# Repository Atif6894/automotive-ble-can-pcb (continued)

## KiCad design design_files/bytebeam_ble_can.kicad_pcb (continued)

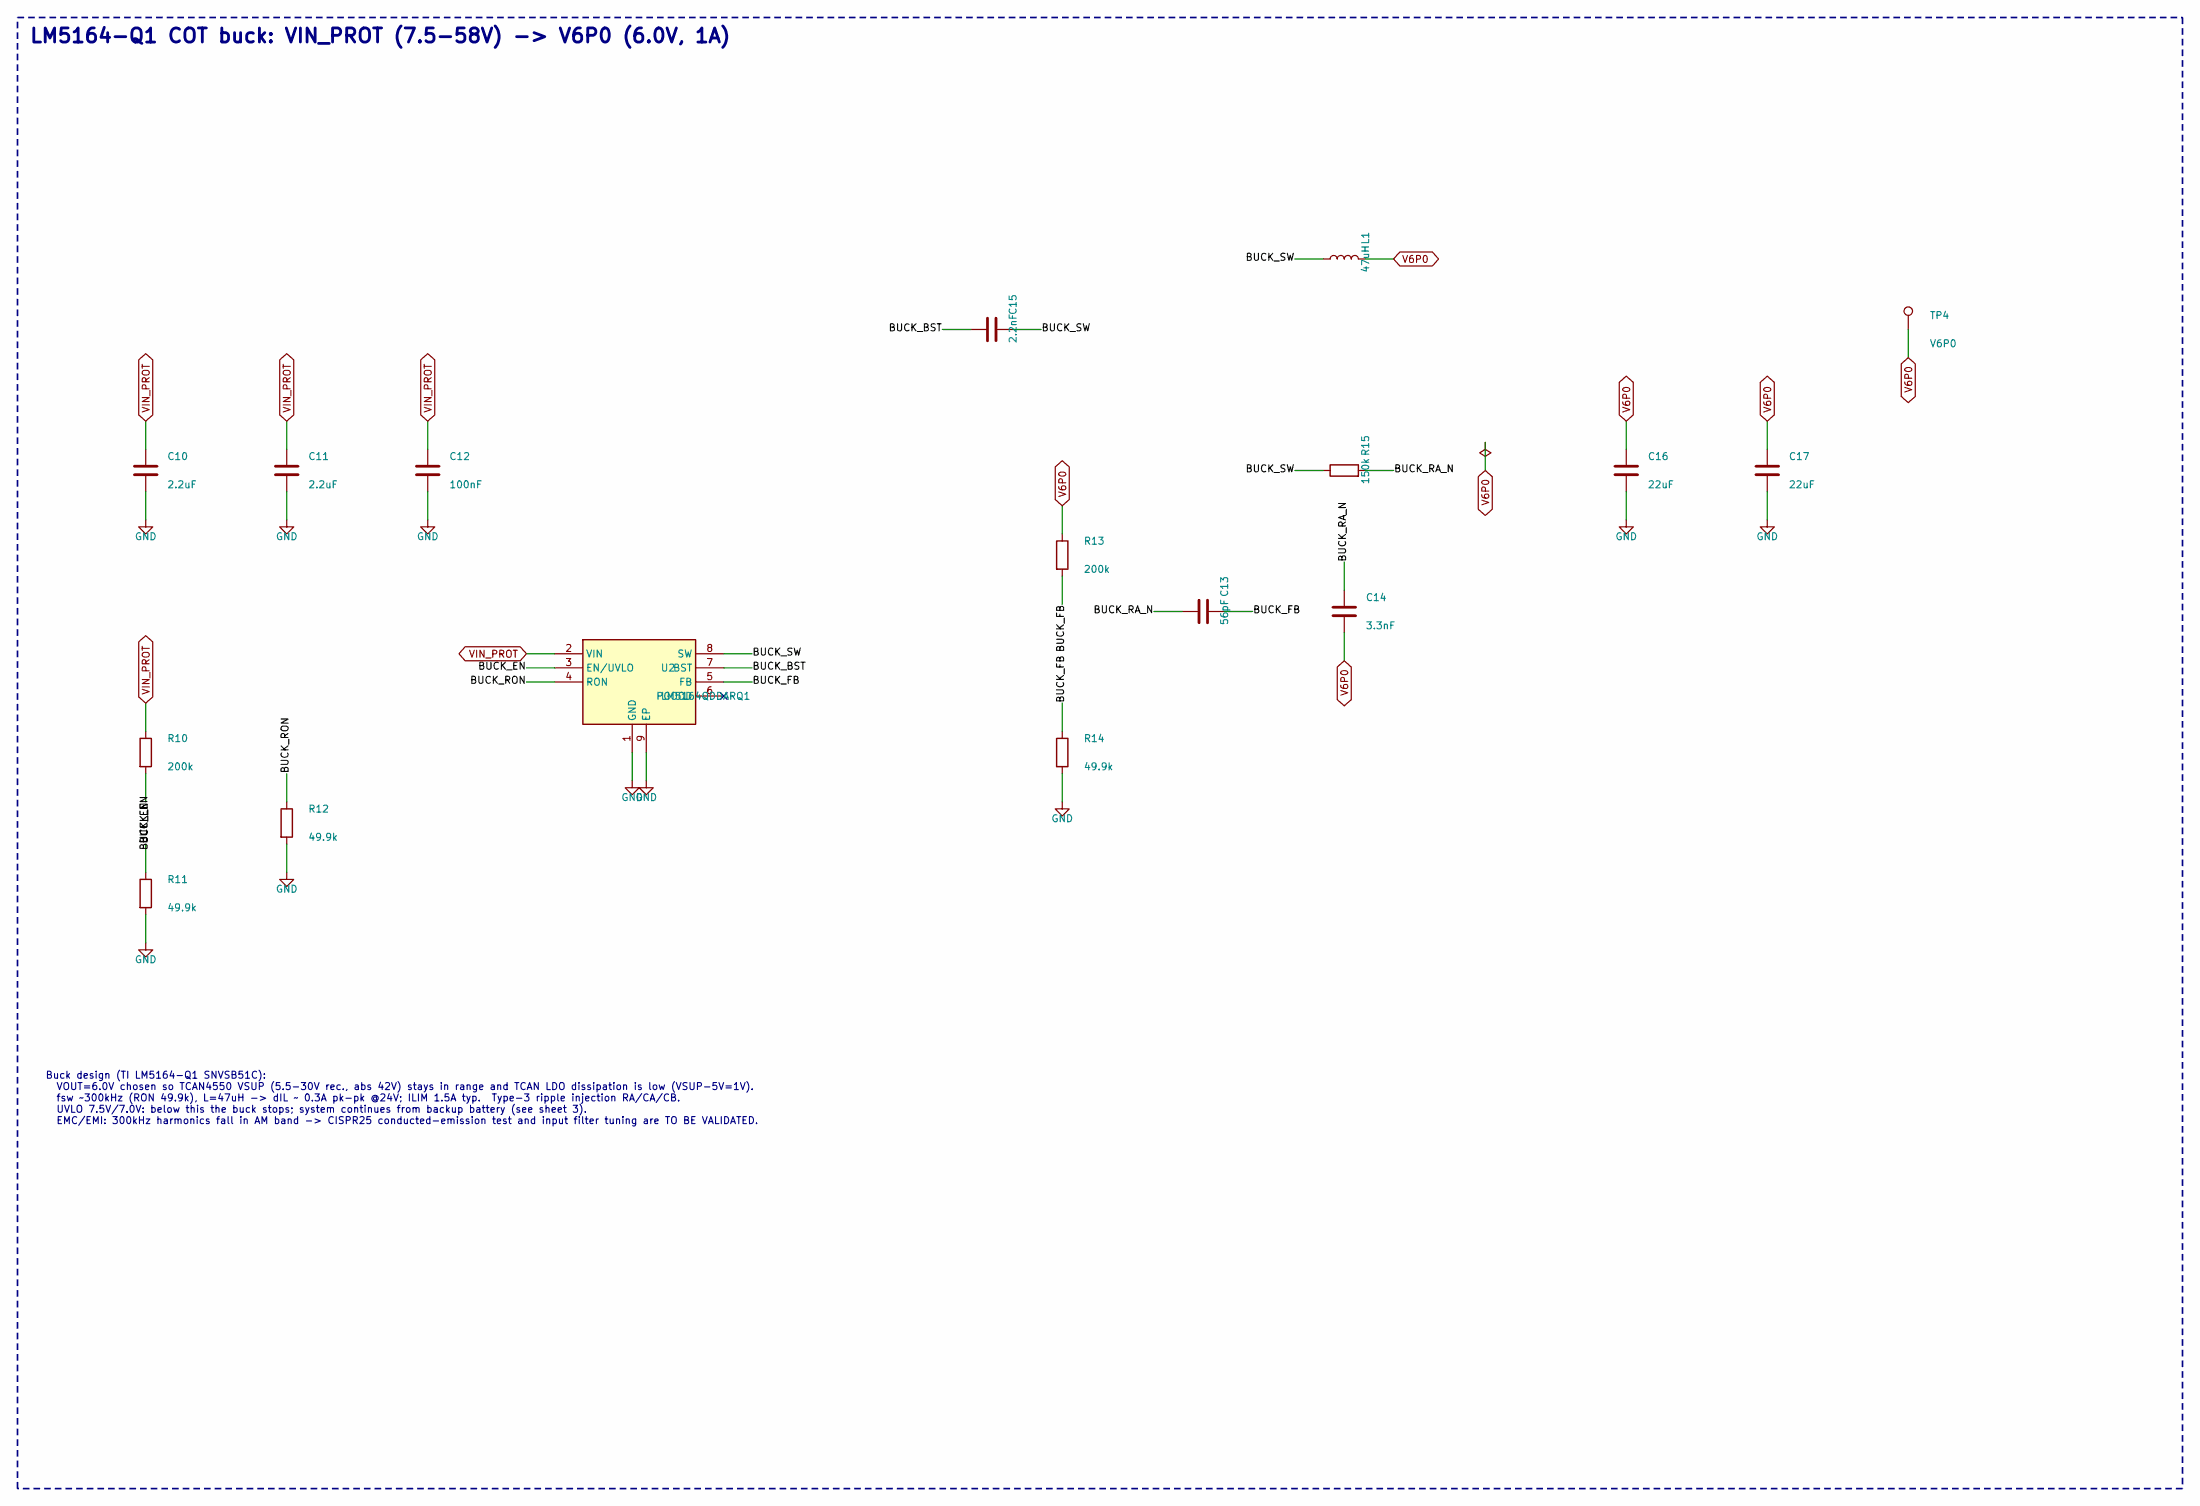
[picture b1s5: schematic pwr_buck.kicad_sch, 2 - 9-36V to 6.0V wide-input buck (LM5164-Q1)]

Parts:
C10, C11: 2.2uF; C_1210_3225Metric; Rating 100V X7R; MPN CGA6N3X7R2A225K230AB
C12: 100nF; C_0603_1608Metric; Rating 100V X7R; MPN GCM-series (AEC-Q200) 100nF 100V X7R
C13: 56pF; C_0402_1005Metric; Rating 50V C0G; MPN C0603C560J5GACTU
C14: 3.3nF; C_0603_1608Metric; Rating 100V X7R; MPN CGA3E2X7R2A332K080AA
C15: 2.2nF; C_0402_1005Metric; Rating 50V X7R; MPN GCM155R71H222KA37D
C16, C17: 22uF; C_1210_3225Metric; Rating 25V X7R; MPN TMK325B7226KMHT
L1: 47uH; L_Coilcraft_XAL6060-XXX; Rating 47uH, Isat 2.5A (20% drop), Irms 3.7A, 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; MPN XGL6060-473MEC
R10: 200k; R_0603_1608Metric; Rating 1% 0.1W; MPN AC0603FR-07200KL
R11, R12, R14: 49.9k; R_0603_1608Metric; Rating 1%, AEC-Q200 thick film; MPN AC0603FR-0749K9L
R13: 200k; R_0603_1608Metric; Rating 1%, AEC-Q200 thick film; MPN AC0603FR-07200KL
R15: 150k; R_0603_1608Metric; Rating 1%, AEC-Q200 thick film; MPN AC0603FR-07150KL
TP4: V6P0; TestPoint_Pad_D1.5mm; Rating bare copper pad; MPN PCB test pad D1.5mm
U2: LM5164QDDARQ1; Texas_HSOP-8-1EP_3.9x4.9mm_P1.27mm; Rating VIN 6-100V, 1A, AEC-Q100 grade 1, Tj -4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; MPN LM5164QDDARQ1

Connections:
/2_Buck_6V0/BUCK_BST: C15.1, U2.7 (BST)
/2_Buck_6V0/BUCK_EN: R10.2, R11.1, U2.3 (EN/UVLO)
/2_Buck_6V0/BUCK_FB: C13.2, R13.2, R14.1, U2.5 (FB)
/2_Buck_6V0/BUCK_RA_N: C13.1, C14.1, R15.2
/2_Buck_6V0/BUCK_RON: R12.1, U2.4 (RON)
/2_Buck_6V0/BUCK_SW: C15.2, L1.1, R15.1, U2.8 (SW)
GND: C10.2, C11.2, C12.2, C16.2, C17.2, R11.2, R12.2, R14.2, U2.1 (GND), U2.9 (EP); also elsewhere on the board
V6P0: C14.2, C16.1, C17.1, L1.2, R13.1, TP4.1; also elsewhere on the board
VIN_PROT: C10.1, C11.1, C12.1, R10.1, U2.2 (VIN); also elsewhere on the board

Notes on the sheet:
LM5164-Q1 COT buck: VIN_PROT (7.5-58V) -> V6P0 (6.0V, 1A)
Buck design (TI LM5164-Q1 SNVSB51C): VOUT=6.0V chosen so TCAN4550 VSUP (5.5-30V rec., abs 42V) stays in range and TCAN LDO dissipation is low (VSUP-5V=1V). fsw ~300kHz (RON 49.9k), L=47uH -> dIL ~ 0.3A pk-pk @24V; ILIM 1.5A typ. Type-3 ripple injection RA/CA/CB. UVLO 7.5V/7.0V: below this the buck 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

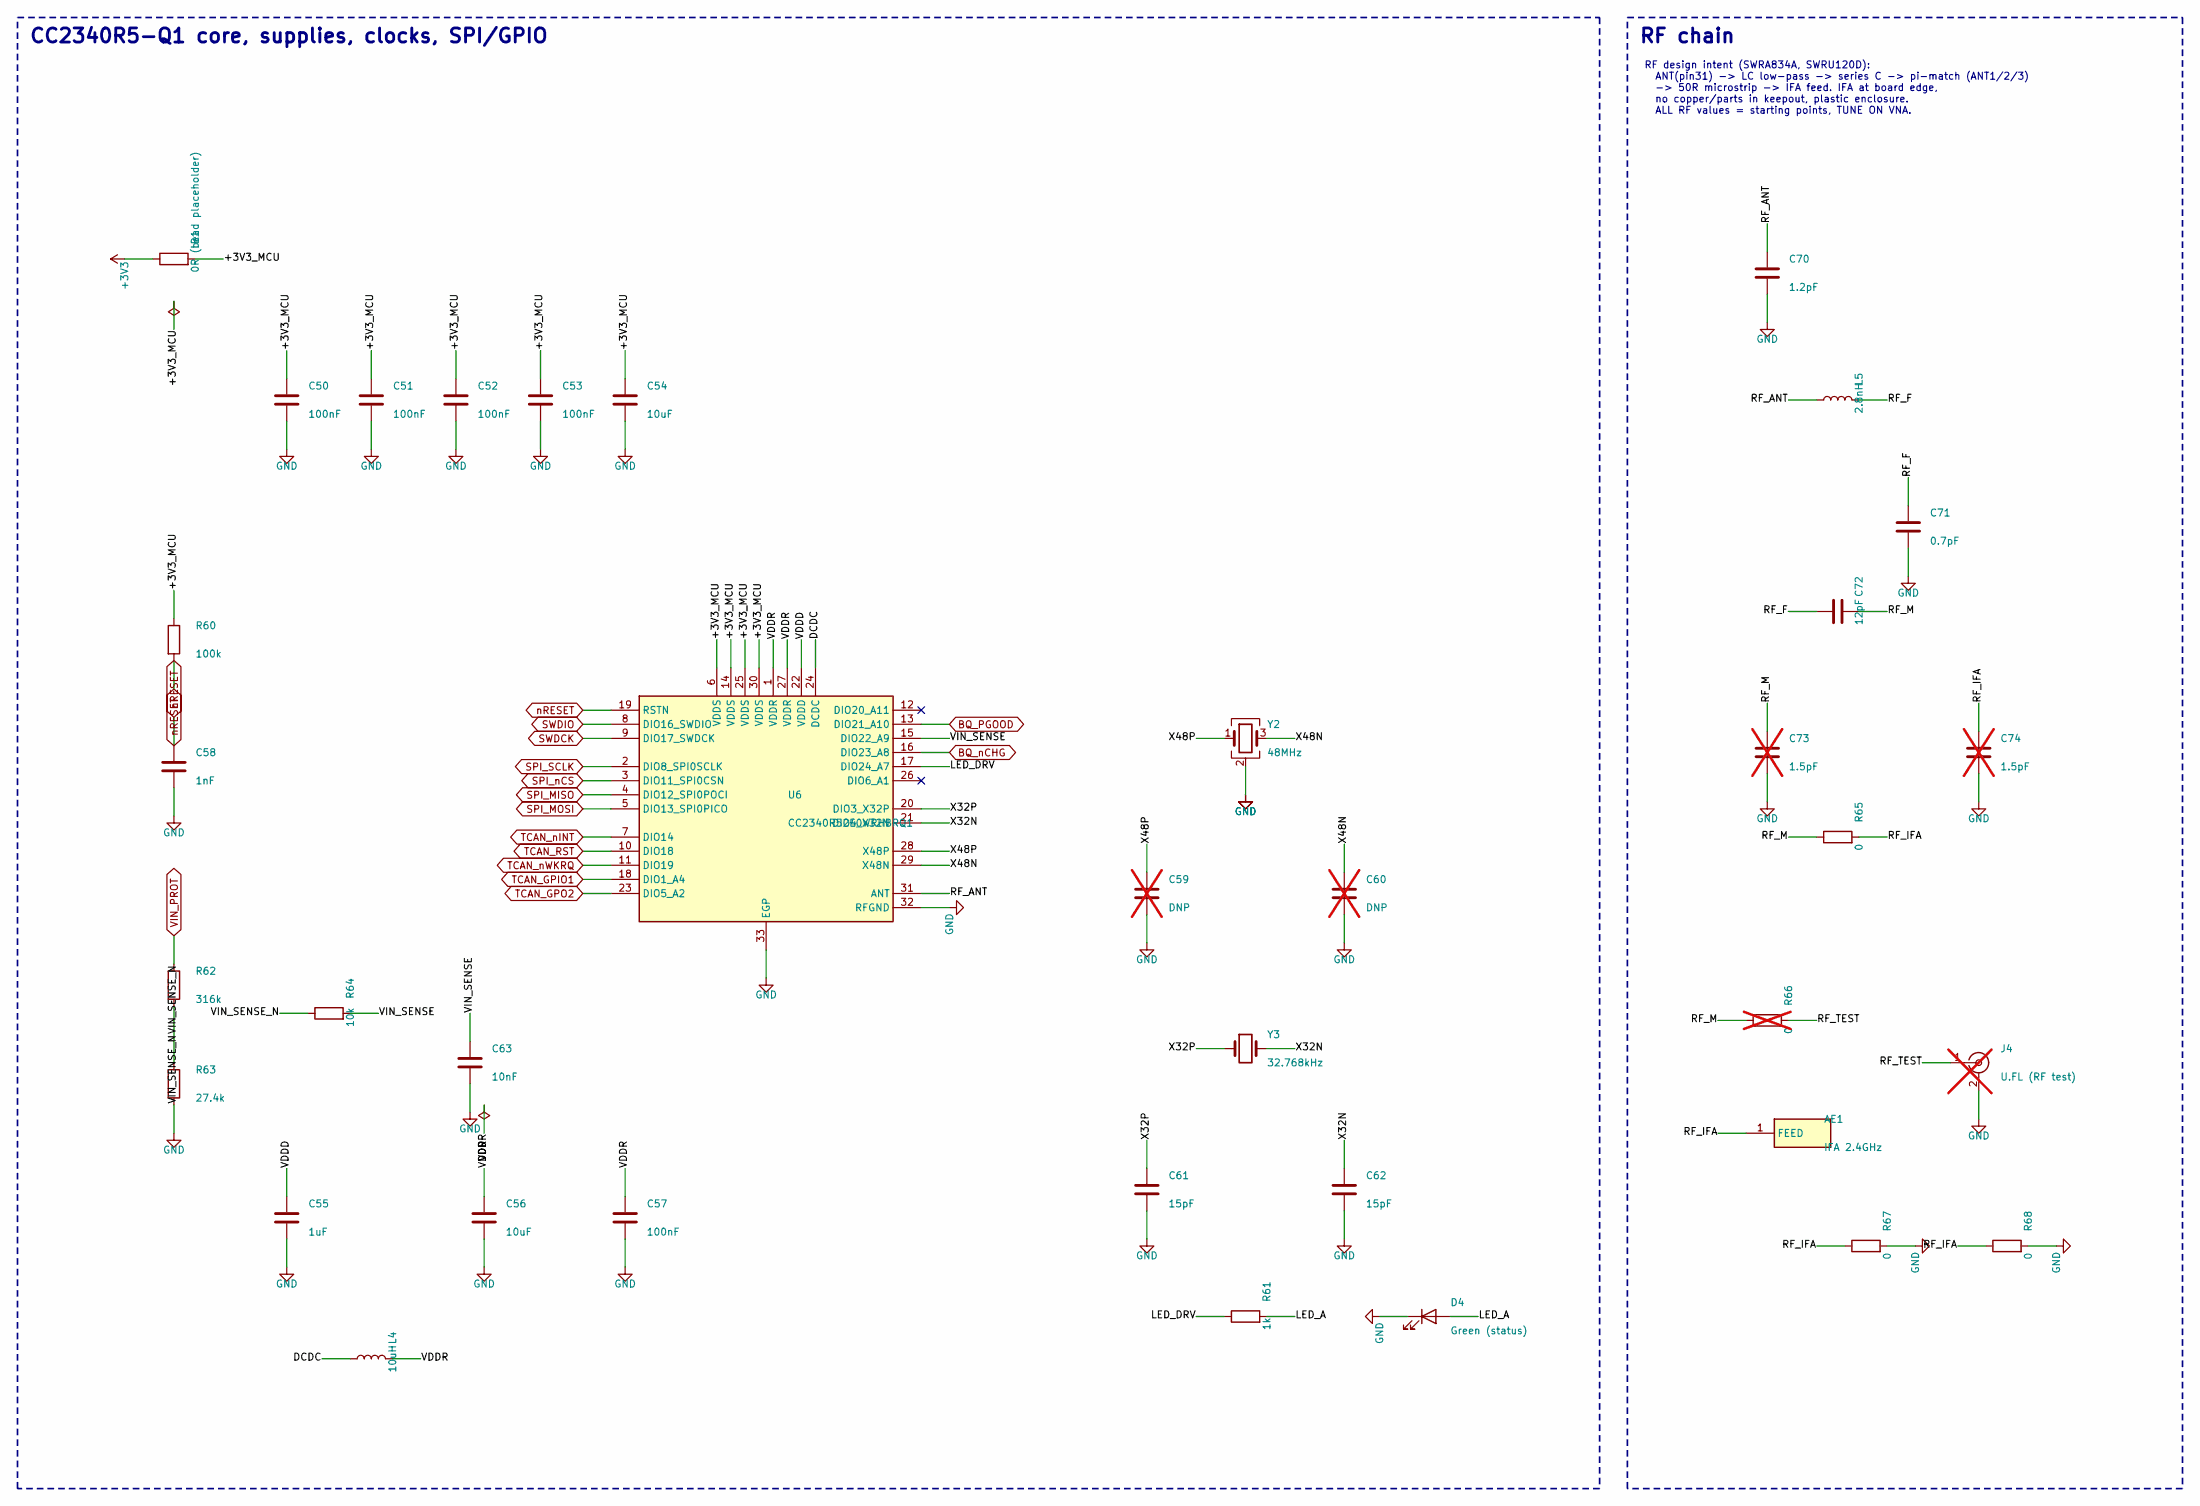
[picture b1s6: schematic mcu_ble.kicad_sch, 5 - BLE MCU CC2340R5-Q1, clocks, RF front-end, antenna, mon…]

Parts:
AE1: IFA 2.4GHz; ANT_IFA_TI_SWRU120_2G4; Rating PCB antenna, gain +3.3dBi max (TI meas.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; MPN TI SWRU120D inverted-F, 25.7x7.5mm
B1: 0R (bead placeholder); R_0402_1005Metric; Rating 0R link / optional ferrite bead (TI ref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; MPN AC0402JR-070RL
C50, C51, C52, C53: 100nF; C_0402_1005Metric; Rating 16V X7R; MPN GCM-series (AEC-Q200) 100nF 16V X7R
C54, C56: 10uF; C_0805_2012Metric; Rating 10V X7R; MPN GCM-series (AEC-Q200) 10uF 10V X7R
C55: 1uF; C_0402_1005Metric; Rating 10V X7R; MPN GCM-series (AEC-Q200) 1uF 10V X7R
C57: 100nF; C_0402_1005Metric; Rating 10V X7R; MPN GCM-series (AEC-Q200) 100nF 10V X7R
C58: 1nF; C_0402_1005Metric; Rating 16V X7R; MPN GCM-series (AEC-Q200) 1nF 16V X7R
C59, C60: DNP; C_0402_1005Metric; Rating 50V C0G; MPN GCM-series (AEC-Q200) DNP 50V C0G; not fitted
C61, C62: 15pF; C_0402_1005Metric; Rating 50V C0G; MPN GCM-series (AEC-Q200) 15pF 50V C0G
C63: 10nF; C_0402_1005Metric; Rating 16V X7R; MPN GCM-series (AEC-Q200) 10nF 16V X7R
C70: 1.2pF; C_0402_1005Metric; Rating C0G +/-0.1pF; MPN GCM-series (AEC-Q200) 1.2pF 50V C0G
C71: 0.7pF; C_0402_1005Metric; Rating C0G +/-0.05pF; MPN GCM-series (AEC-Q200) 0.7pF 50V C0G
C72: 12pF; C_0402_1005Metric; Rating 50V C0G; MPN GCM-series (AEC-Q200) 12pF 50V C0G
C73, C74: 1.5pF; C_0402_1005Metric; Rating 50V C0G; MPN GCM-series (AEC-Q200) 1.5pF 50V C0G; not fitted
D4: Green (status); LED_0603_1608Metric; Rating 0603 green (AEC-Q101 variant to select); MPN LTST-C193KGKT-5A
J4: U.FL (RF test); U.FL_Hirose_U.FL-R-SMT-1_Vertical; Rating 6GHz, conducted RF/BLE test only, DNP i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; MPN U.FL-R-SMT-1(10); not fitted
L4: 10uH; L_0805_2012Metric; MPN LQM21PN100MGRD or equiv. (10uH, >=150mA)
L5: 2.8nH; L_0402_1005Metric; MPN LQP15MN2N8B02D (2.8nH class)
R60: 100k; R_0402_1005Metric; Rating 1%, AEC-Q200 thick film; MPN AC0402FR-07100KL
R61: 1k; R_0402_1005Metric; Rating 1%, AEC-Q200 thick film; MPN AC0402FR-071KL
R62: 316k; R_0603_1608Metric; Rating 1%, AEC-Q200 thick film; MPN AC0603FR-07316KL
R63: 27.4k; R_0603_1608Metric; Rating 1%, AEC-Q200 thick film; MPN AC0603FR-0727K4L
R64: 10k; R_0402_1005Metric; Rating 1%, AEC-Q200 thick film; MPN AC0402FR-0710KL
R65: 0; R_0402_1005Metric; Rating 0R 0402; MPN AC0402FR-070RL
R66: 0; R_0402_1005Metric; Rating 1%, AEC-Q200 thick film; MPN AC0402FR-070RL; not fitted
R67, R68: 0; R_0402_1005Metric; Rating 1%, AEC-Q200 thick film; MPN AC0402FR-070RL
U6: CC2340R52E0WRHBRQ1; QFN-32-1EP_5x5mm_P0.5mm_EP3.7x3.7mm; Rating AEC-Q100 -40..125C, VDDS 1.71-3.8V, 512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; MPN CC2340R52E0WRHBRQ1
Y2: 48MHz; Crystal_SMD_2016-4Pin_2.0x1.6mm; Rating 48MHz +/-5ppm, CL 7pF, ESR 30R (validat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; MPN TZ3908AAAO43
Y3: 32.768kHz; Crystal_SMD_3215-2Pin_3.2x1.5mm; Rating CL 6-12pF supported, ESR 30-100k (SWRS2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; MPN FC-135R 32.768kHz 9pF (TBC)

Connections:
+3V3: B1.1; also elsewhere on the board
/5_MCU_BLE_RF/+3V3_MCU: B1.2, C50.1, C51.1, C52.1, C53.1, C54.1, R60.1, U6.6 (VDDS), U6.14 (VDDS), U6.25 (VDDS), U6.30 (VDDS)
/5_MCU_BLE_RF/DCDC: L4.1, U6.24 (DCDC)
/5_MCU_BLE_RF/LED_A: D4.2 (A), R61.2
/5_MCU_BLE_RF/LED_DRV: R61.1, U6.17 (DIO24_A7)
/5_MCU_BLE_RF/RF_ANT: C70.1, L5.1, U6.31 (ANT)
/5_MCU_BLE_RF/RF_F: C71.1, C72.1, L5.2
/5_MCU_BLE_RF/RF_IFA: AE1.1, C74.1, R65.2, R67.1, R68.1
/5_MCU_BLE_RF/RF_M: C72.2, C73.1, R65.1, R66.1
/5_MCU_BLE_RF/RF_TEST: J4.1 (In), R66.2
/5_MCU_BLE_RF/VDDD: C55.1, U6.22 (VDDD)
/5_MCU_BLE_RF/VDDR: C56.1, C57.1, L4.2, U6.1 (VDDR), U6.27 (VDDR)
/5_MCU_BLE_RF/VIN_SENSE: C63.1, R64.2, U6.15 (DIO22_A9)
/5_MCU_BLE_RF/VIN_SENSE_N: R62.2, R63.1, R64.1
/5_MCU_BLE_RF/X32N: C62.1, U6.21 (DIO4_X32N), Y3.2
/5_MCU_BLE_RF/X32P: C61.1, U6.20 (DIO3_X32P), Y3.1
/5_MCU_BLE_RF/X48N: C60.1, U6.29 (X48N), Y2.3
/5_MCU_BLE_RF/X48P: C59.1, U6.28 (X48P), Y2.1
BQ_PGOOD: U6.13 (DIO21_A10); also elsewhere on the board
BQ_nCHG: U6.16 (DIO23_A8); also elsewhere on the board
GND: C50.2, C51.2, C52.2, C53.2, C54.2, C55.2, C56.2, C57.2, C58.2, C59.2, C60.2, C61.2, C62.2, C63.2, C70.2, C71.2, C73.2, C74.2, D4.1 (K), J4.2 (Ext), R63.2, R67.2, R68.2, U6.32 (RFGND), U6.33 (EGP), Y2.2 (G), Y2.4 (G); also elsewhere on the board
SPI_MISO: U6.4 (DIO12_SPI0POCI); also elsewhere on the board
SPI_MOSI: U6.5 (DIO13_SPI0PICO); also elsewhere on the board
SPI_SCLK: U6.2 (DIO8_SPI0SCLK); also elsewhere on the board
SPI_nCS: U6.3 (DIO11_SPI0CSN); also elsewhere on the board
SWDCK: U6.9 (DIO17_SWDCK); also elsewhere on the board
SWDIO: U6.8 (DIO16_SWDIO); also elsewhere on the board
TCAN_GPIO1: U6.18 (DIO1_A4); also elsewhere on the board
TCAN_GPO2: U6.23 (DIO5_A2); also elsewhere on the board
TCAN_RST: U6.10 (DIO18); also elsewhere on the board
TCAN_nINT: U6.7 (DIO14); also elsewhere on the board
TCAN_nWKRQ: U6.11 (DIO19); also elsewhere on the board
VIN_PROT: R62.1; also elsewhere on the board
nRESET: C58.1, R60.2, U6.19 (RSTN); also elsewhere on the board

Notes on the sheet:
CC2340R5-Q1 core, supplies, clocks, SPI/GPIO
RF design intent (SWRA834A, SWRU120D): ANT(pin31) -> LC low-pass -> series C -> pi-match (ANT1/2/3) -> 50R microstrip -> IFA feed. IFA at board edge, no copper/parts in keepout, plastic enclosure. ALL RF values = starting points, TUNE ON VNA.
RF chain

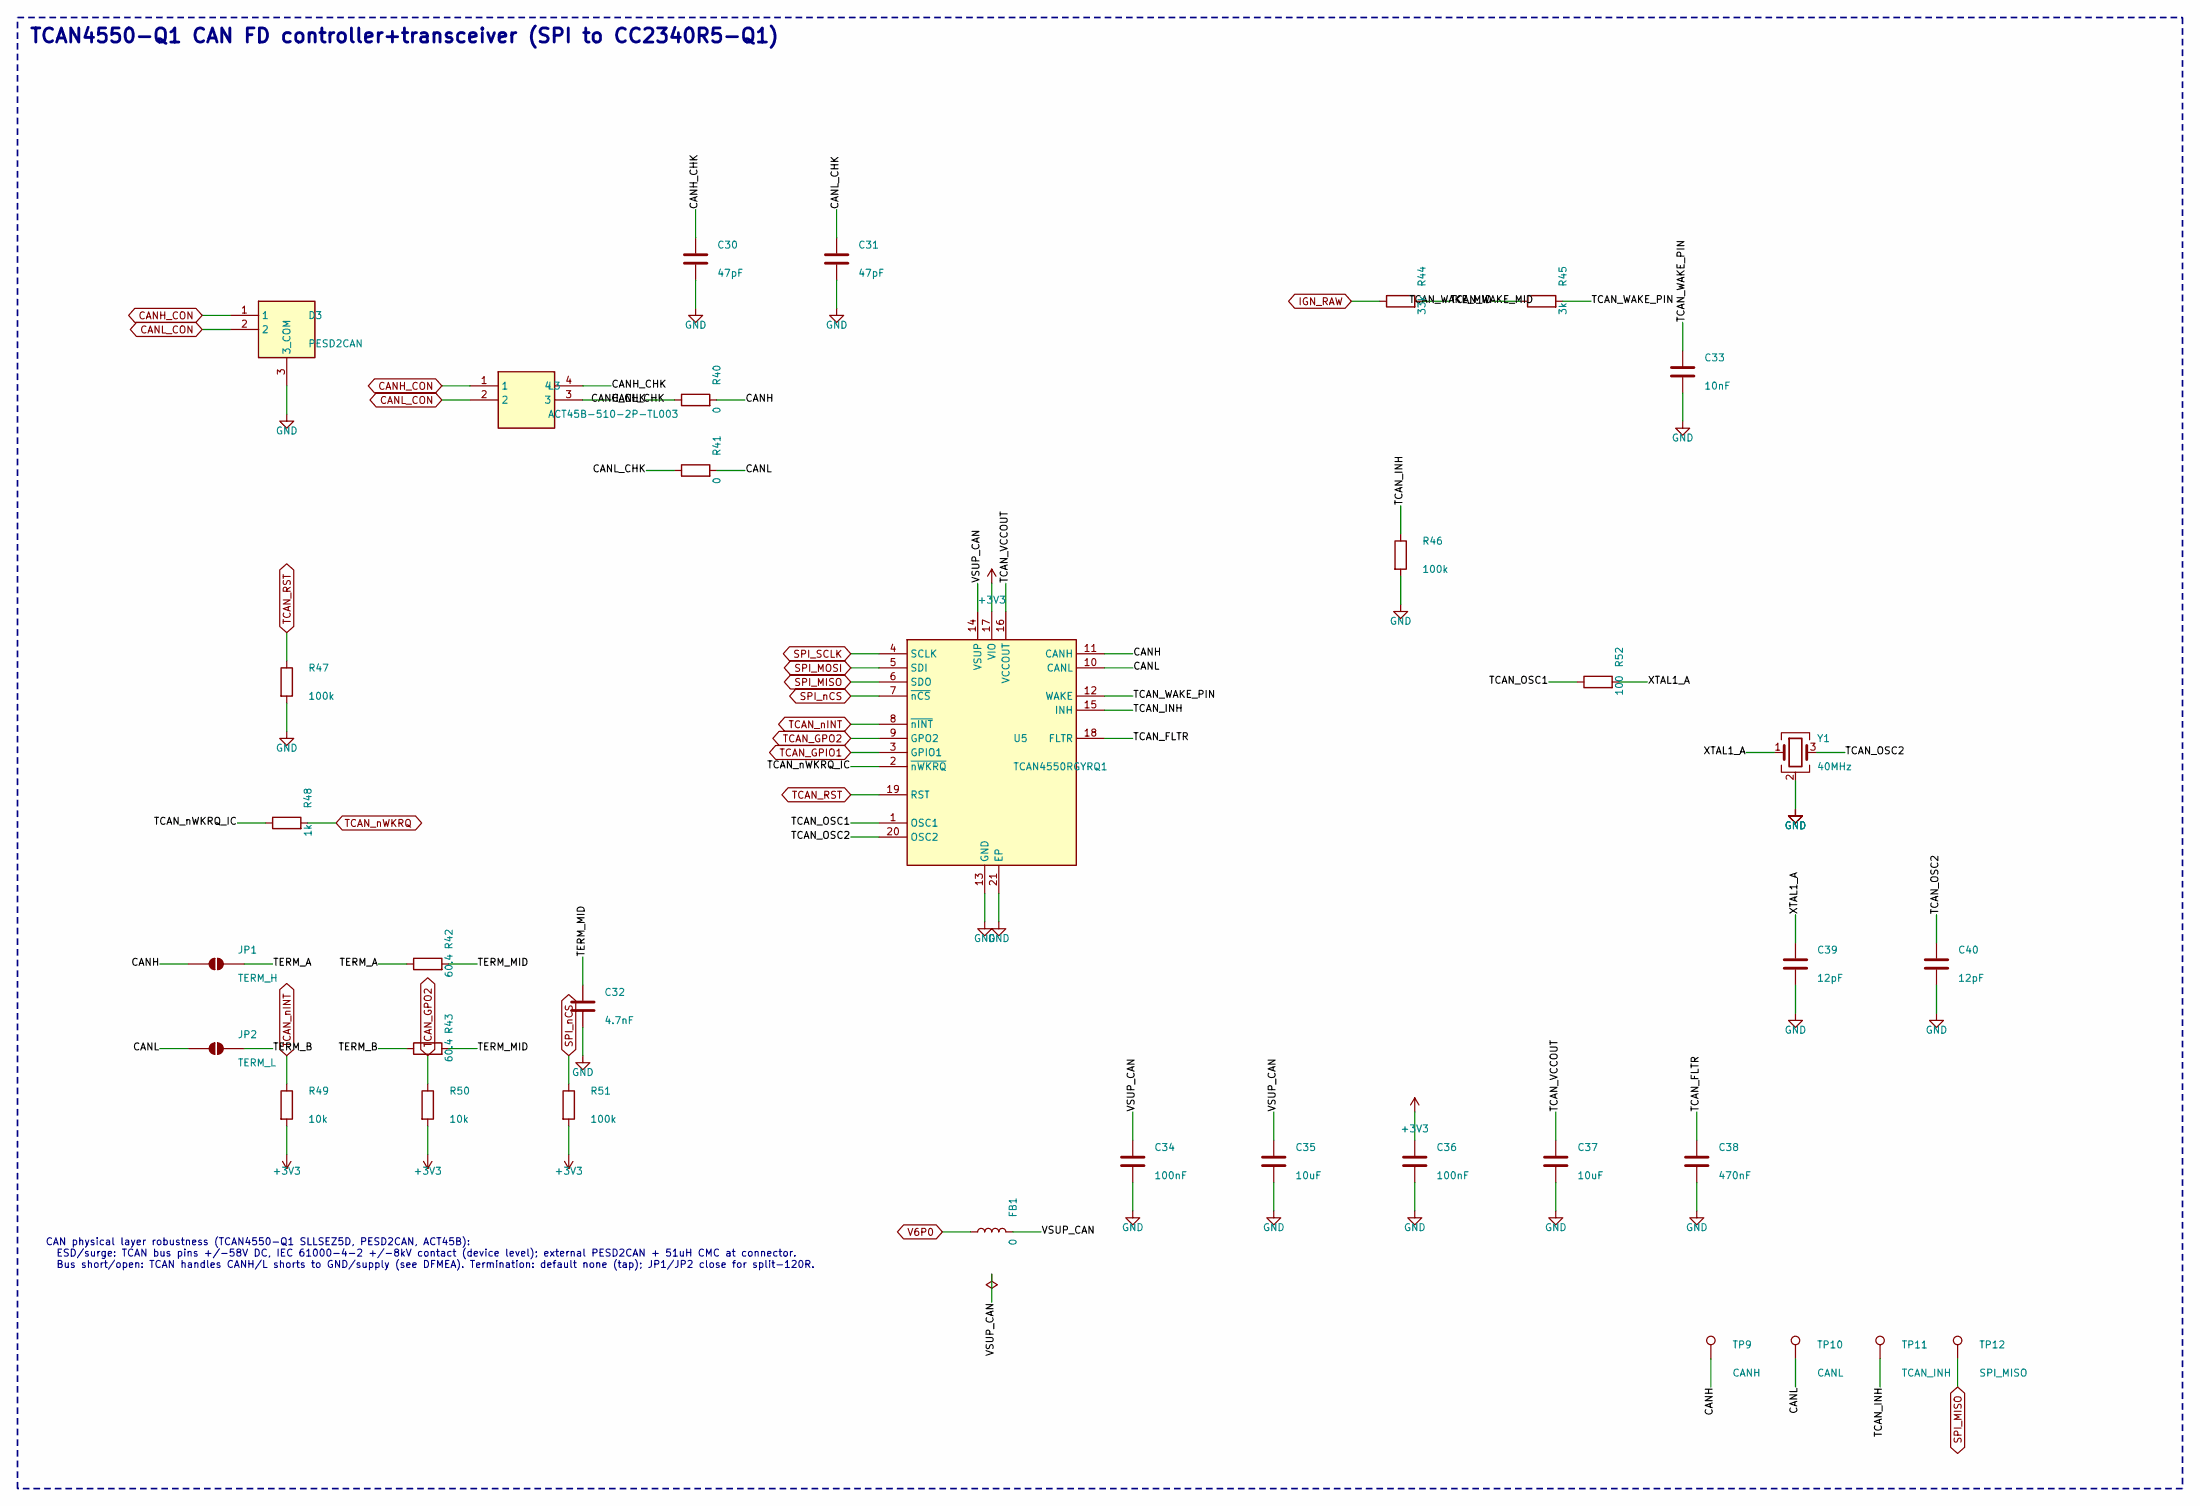
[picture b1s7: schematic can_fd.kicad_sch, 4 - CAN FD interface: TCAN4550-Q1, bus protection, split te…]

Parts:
C30, C31: 47pF; C_0603_1608Metric; Rating 100V C0G; MPN GCM-series (AEC-Q200) 47pF 100V C0G
C32: 4.7nF; C_0603_1608Metric; Rating 100V C0G/X7R; MPN GCM-series (AEC-Q200) 4.7nF 100V C0G/X7R
C33: 10nF; C_0603_1608Metric; Rating 50V X7R; MPN GCM-series (AEC-Q200) 10nF 50V X7R
C34: 100nF; C_0603_1608Metric; Rating 50V X7R; MPN GCM-series (AEC-Q200) 100nF 50V X7R
C35, C37: 10uF; C_0805_2012Metric; Rating 16V X7R; MPN GCM-series (AEC-Q200) 10uF 16V X7R
C36: 100nF; C_0402_1005Metric; Rating 16V X7R; MPN GCM-series (AEC-Q200) 100nF 16V X7R
C38: 470nF; C_0603_1608Metric; Rating 16V X7R; MPN GCM-series (AEC-Q200) 470nF 16V X7R
C39, C40: 12pF; C_0402_1005Metric; Rating 50V C0G; MPN GCM-series (AEC-Q200) 12pF 50V C0G
D3: PESD2CAN; SOT-23; Rating VRWM 24V, Vcl 41V @5A, 30kV ESD, AEC-Q1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; MPN PESD2CAN,215
FB1: 0; L_0603_1608Metric; MPN BLM18PG221SN1D
JP1: TERM_H; SolderJumper-2_P1.3mm_Open_RoundedPad1.0x1.5mm; Rating closed by solder blob; MPN solder jumper (open)
JP2: TERM_L; SolderJumper-2_P1.3mm_Open_RoundedPad1.0x1.5mm; Rating closed by solder blob; MPN solder jumper (open)
L3: ACT45B-510-2P-TL003; CMC_TDK_ACT45B_EIA1812; Rating 51uH, 50VDC, 200mA, AEC-Q200, -40..150C; MPN ACT45B-510-2P-TL003
R40, R41: 0; R_0603_1608Metric; Rating 1%, AEC-Q200 thick film; MPN AC0603FR-070RL
R42, R43: 60.4; R_0805_2012Metric; Rating 0.25W 1% AEC-Q200; MPN AC0805FR-0760R4L
R44: 33k; R_0603_1608Metric; Rating 1%, AEC-Q200 thick film; MPN AC0603FR-0733KL
R45: 3k; R_0603_1608Metric; Rating 1%, AEC-Q200 thick film; MPN AC0603FR-073KL
R46, R47, R51: 100k; R_0402_1005Metric; Rating 1%, AEC-Q200 thick film; MPN AC0402FR-07100KL
R48: 1k; R_0402_1005Metric; Rating 1%, AEC-Q200 thick film; MPN AC0402FR-071KL
R49, R50: 10k; R_0402_1005Metric; Rating 1%, AEC-Q200 thick film; MPN AC0402FR-0710KL
R52: 100; R_0402_1005Metric; Rating 1%, AEC-Q200 thick film; MPN AC0402FR-07100RL
TP9: CANH; TestPoint_Pad_D1.5mm; Rating bare copper pad; MPN PCB test pad D1.5mm
TP10: CANL; TestPoint_Pad_D1.5mm; Rating bare copper pad; MPN PCB test pad D1.5mm
TP11: TCAN_INH; TestPoint_Pad_D1.5mm; Rating bare copper pad; MPN PCB test pad D1.5mm
TP12: SPI_MISO; TestPoint_Pad_D1.5mm; Rating bare copper pad; MPN PCB test pad D1.5mm
U5: TCAN4550RGYRQ1; Texas_RGY_R-PVQFN-N20_EP2.05x3.05mm; Rating VSUP 5.5-30V (42V abs), VIO 3.135-5.25V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; MPN TCAN4550RGYRQ1
Y1: 40MHz; Crystal_SMD_3225-4Pin_3.2x2.5mm; Rating 40MHz, CL~8pF, ESR<=60R (TCAN spec), +/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; MPN NX3225GD-40.000M-xxx (order code TBC)

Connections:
+3V3: C36.1, R49.2, R50.2, R51.2, U5.17 (VIO); also elsewhere on the board
/4_CAN_FD/CANH: JP1.1 (A), R40.2, TP9.1, U5.11 (CANH)
/4_CAN_FD/CANH_CHK: C30.1, L3.4, R40.1
/4_CAN_FD/CANL: JP2.1 (A), R41.2, TP10.1, U5.10 (CANL)
/4_CAN_FD/CANL_CHK: C31.1, L3.3, R41.1
/4_CAN_FD/TCAN_FLTR: C38.1, U5.18 (FLTR)
/4_CAN_FD/TCAN_INH: R46.1, TP11.1, U5.15 (INH)
/4_CAN_FD/TCAN_OSC1: R52.1, U5.1 (OSC1)
/4_CAN_FD/TCAN_OSC2: C40.1, U5.20 (OSC2), Y1.3
/4_CAN_FD/TCAN_VCCOUT: C37.1, U5.16 (VCCOUT)
/4_CAN_FD/TCAN_WAKE_MID: R44.2, R45.1
/4_CAN_FD/TCAN_WAKE_PIN: C33.1, R45.2, U5.12 (WAKE)
/4_CAN_FD/TCAN_nWKRQ_IC: R48.1, U5.2 (~nWKRQ)
/4_CAN_FD/TERM_A: JP1.2 (B), R42.1
/4_CAN_FD/TERM_B: JP2.2 (B), R43.1
/4_CAN_FD/TERM_MID: C32.1, R42.2, R43.2
/4_CAN_FD/VSUP_CAN: C34.1, C35.1, FB1.2, U5.14 (VSUP)
/4_CAN_FD/XTAL1_A: C39.1, R52.2, Y1.1
CANH_CON: D3.1, L3.1; also elsewhere on the board
CANL_CON: D3.2, L3.2; also elsewhere on the board
GND: C30.2, C31.2, C32.2, C33.2, C34.2, C35.2, C36.2, C37.2, C38.2, C39.2, C40.2, D3.3 (3_COM), R46.2, R47.2, U5.13 (GND), U5.21 (EP), Y1.2 (G), Y1.4 (G); also elsewhere on the board
IGN_RAW: R44.1; also elsewhere on the board
SPI_MISO: TP12.1, U5.6 (SDO); also elsewhere on the board
SPI_MOSI: U5.5 (SDI); also elsewhere on the board
SPI_SCLK: U5.4 (SCLK); also elsewhere on the board
SPI_nCS: R51.1, U5.7 (~nCS); also elsewhere on the board
TCAN_GPIO1: U5.3 (GPIO1); also elsewhere on the board
TCAN_GPO2: R50.1, U5.9 (GPO2); also elsewhere on the board
TCAN_RST: R47.1, U5.19 (RST); also elsewhere on the board
TCAN_nINT: R49.1, U5.8 (~nINT); also elsewhere on the board
TCAN_nWKRQ: R48.2; also elsewhere on the board
V6P0: FB1.1; also elsewhere on the board

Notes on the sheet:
CAN physical layer robustness (TCAN4550-Q1 SLLSEZ5D, PESD2CAN, ACT45B): ESD/surge: TCAN bus pins +/-58V DC, IEC 61000-4-2 +/-8kV contact (device level); external PESD2CAN + 51uH CMC at connector. Bus short/open: TCAN handles CANH/L shorts to GND/supply (see DFMEA). Termination: default none (tap); 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
TCAN4550-Q1 CAN FD controller+transceiver (SPI to CC2340R5-Q1)

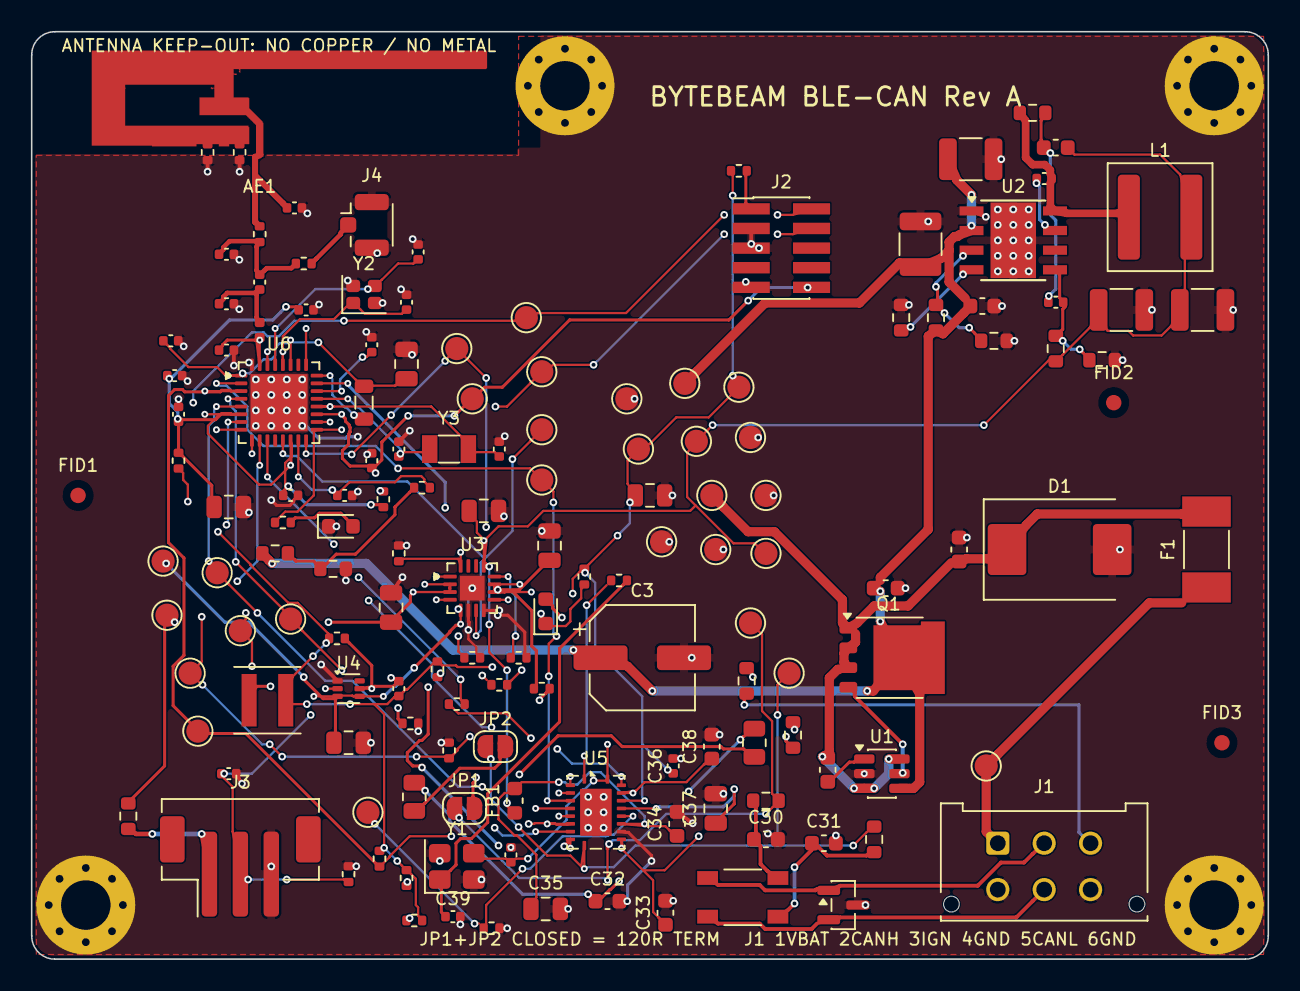
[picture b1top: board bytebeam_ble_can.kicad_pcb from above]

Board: 4 copper layers, 80.0 x 60.0 mm, 153 parts (0 on the bottom side), 76 nets.

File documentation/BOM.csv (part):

Refs,Qty,Value,Package/Footprint,Manufacturer,MPN,Ratings / qualification,MPN status,Key alternatives,Fit,Notes / unresolved assumptions
AE1,1,IFA 2.4GHz,ANT_IFA_TI_SWRU120_2G4,PCB,"TI SWRU120D inverted-F, 25.7x7.5mm","PCB antenna, gain +3.3dBi max (TI meas., 1mm FR4 ref board)",VERIFIED,,Fit,Geometry reproduced from TI SWRU120D Figure 1-1 / Table 1-1; performance on this stackup is UNVERIFIED.
B1,1,0R (bead placeholder),R_0402_1005Metric,Yageo,AC0402JR-070RL,0R link / optional ferrite bead (TI ref design 'B1'),FAMILY,,Fit,
C1,1,47nF,C_0603_1608Metric,Murata,GCM-series (AEC-Q200) 47nF 100V X7R,100V X7R,FAMILY,TDK CGA / Samsung CL-AEC (AEC-Q200),Fit,LM74700 ANODE-side capacitance (>=22nF) - TI datasheet 6.3
C2,1,100nF,C_0603_1608Metric,Murata,GCM-series (AEC-Q200) 100nF 25V X7R,25V X7R,FAMILY,TDK CGA / Samsung CL-AEC (AEC-Q200),Fit,Charge-pump reservoir VCAP-ANODE (>=0.1uF) - TI datasheet 6.3
C3,1,33uF,CP_Elec_6.3x5.8,Panasonic,EEE-FN1H330P,50V X7R,FAMILY,TDK CGA / Samsung CL-AEC (AEC-Q200),Fit,"Bulk cap / hold-up damping for buck input (6.3x5.8mm, 105C limit - derate ripple; consider 125C polymer hybrid for final)."
"C4,C12",2,100nF,C_0603_1608Metric,Murata,GCM-series (AEC-Q200) 100nF 100V X7R,100V X7R,FAMILY,TDK CGA / Samsung CL-AEC (AEC-Q200),Fit,
"C10,C11",2,2.2uF,C_1210_3225Metric,TDK,CGA6N3X7R2A225K230AB,100V X7R,VERIFIED,TDK CGA / Samsung CL-AEC (AEC-Q200),Fit,Input cap per TI LM5164-Q1 datasheet Table 7-1 (2 needed)
C13,1,56pF,C_0402_1005Metric,Kemet,C0603C560J5GACTU,50V C0G,VERIFIED,TDK CGA / Samsung CL-AEC (AEC-Q200),Fit,"Type-3 ripple network CB (TI: C0G/NP0 required); 0603 in TI BOM, 0402 footprint pattern to be aligned at sourcing"
C14,1,3.3nF,C_0603_1608Metric,TDK,CGA3E2X7R2A332K080AA,100V X7R,VERIFIED,TDK CGA / Samsung CL-AEC (AEC-Q200),Fit,Type-3 ripple network CA
C15,1,2.2nF,C_0402_1005Metric,Murata,GCM155R71H222KA37D,50V X7R,VERIFIED,TDK CGA / Samsung CL-AEC (AEC-Q200),Fit,Bootstrap cap 2.2nF/50V X7R - required value per datasheet pin table
"C16,C17",2,22uF,C_1210_3225Metric,Taiyo Yuden,TMK325B7226KMHT,25V X7R,VERIFIED,TDK CGA / Samsung CL-AEC (AEC-Q200),Fit,COUT per TI Table 7-1 (2x)
C20,1,4.7uF,C_0805_2012Metric,Murata,GCM-series (AEC-Q200) 4.7uF 16V X7R,16V X7R,FAMILY,TDK CGA / Samsung CL-AEC (AEC-Q200),Fit,IN bypass 1-10uF (TI)
"C21,C22,C54,C56",4,10uF,C_0805_2012Metric,Murata,GCM-series (AEC-Q200) 10uF 10V X7R,10V X7R,FAMILY,TDK CGA / Samsung CL-AEC (AEC-Q200),Fit,BAT bypass 4.7-47uF (TI) | OUT bypass 4.7-47uF (TI) | VDDR 10uF load capacitor (SWRS292A pin 27 / datasheet 7.4 note) | VDDS bulk (TI ref C104 10uF)
"C23,C63",2,10nF,C_0402_1005Metric,Murata,GCM-series (AEC-Q200) 10nF 16V X7R,16V X7R,FAMILY,TDK CGA / Samsung CL-AEC (AEC-Q200),Fit,TS noise filter
C24,1,4.7uF,C_0805_2012Metric,Murata,GRM21BR71A475KA73L,10V X7R,VERIFIED,TDK CGA / Samsung CL-AEC (AEC-Q200),Fit,C1 per TPS62A01-Q1 Table 8-2
C25,1,22uF,C_0805_2012Metric,Murata,GRM21BZ71A226KE15L,10V X7R,VERIFIED,TDK CGA / Samsung CL-AEC (AEC-Q200),Fit,C2 per TPS62A01-Q1 Table 8-2
C26,1,27pF,C_0402_1005Metric,Murata,GCM-series (AEC-Q200) 27pF 50V C0G,50V C0G,FAMILY,TDK CGA / Samsung CL-AEC (AEC-Q200),Fit,Feed-forward C3: TI recommends 27pF for 3.3V out
"C30,C31",2,47pF,C_0603_1608Metric,Murata,GCM-series (AEC-Q200) 47pF 100V C0G,100V C0G,FAMILY,TDK CGA / Samsung CL-AEC (AEC-Q200),Fit,Optional bus filter (TCAN datasheet 11.1 C10/C11); tune vs EMC results
C32,1,4.7nF,C_0603_1608Metric,Murata,GCM-series (AEC-Q200) 4.7nF 100V C0G/X7R,100V C0G/X7R,FAMILY,TDK CGA / Samsung CL-AEC (AEC-Q200),Fit,Split-termination common-mode capacitor (TCAN datasheet Figure 9-2)
C33,1,10nF,C_0603_1608Metric,Murata,GCM-series (AEC-Q200) 10nF 50V X7R,50V X7R,FAMILY,TDK CGA / Samsung CL-AEC (AEC-Q200),Fit,WAKE 10nF (TCAN datasheet 8.3.6)
C34,1,100nF,C_0603_1608Metric,Murata,GCM-series (AEC-Q200) 100nF 50V X7R,50V X7R,FAMILY,TDK CGA / Samsung CL-AEC (AEC-Q200),Fit,VSUP 100nF (TCAN sec.10)
"C35,C37",2,10uF,C_0805_2012Metric,Murata,GCM-series (AEC-Q200) 10uF 16V X7R,16V X7R,FAMILY,TDK CGA / Samsung CL-AEC (AEC-Q200),Fit,VCCOUT >=10uF after derating (TCAN 6.4); no external load
"C36,C50,C51,C52,C53",5,100nF,C_0402_1005Metric,Murata,GCM-series (AEC-Q200) 100nF 16V X7R,16V X7R,FAMILY,TDK CGA / Samsung CL-AEC (AEC-Q200),Fit,"One 100nF per VDDS pin (pins 6/14/25/30), placed at pin, own GND via (SWRA834A 4.3) | VIO 100nF (TCAN 8.3.2)"
C38,1,470nF,C_0603_1608Metric,Murata,GCM-series (AEC-Q200) 470nF 16V X7R,16V X7R,FAMILY,TDK CGA / Samsung CL-AEC (AEC-Q200),Fit,FLTR >=300nF after derating (TCAN 6.4)
"C39,C40,C72",3,12pF,C_0402_1005Metric,Murata,GCM-series (AEC-Q200) 12pF 50V C0G,50V C0G,ASSUMED,TDK CGA / Samsung CL-AEC (AEC-Q200),Fit,Load cap ASSUMED: CL=(12pF*12pF)/(24pF)+Cstray~8pF | Series DC-block (IFA radiator is DC-shorted to GND): TI ref lists 12pF; function assumed
C55,1,1uF,C_0402_1005Metric,Murata,GCM-series (AEC-Q200) 1uF 10V X7R,10V X7R,FAMILY,TDK CGA / Samsung CL-AEC (AEC-Q200),Fit,VDDD 1uF external decoupling (SWRS292A pin 22)
C57,1,100nF,C_0402_1005Metric,Murata,GCM-series (AEC-Q200) 100nF 10V X7R,10V X7R,FAMILY,TDK CGA / Samsung CL-AEC (AEC-Q200),Fit,
C58,1,1nF,C_0402_1005Metric,Murata,GCM-series (AEC-Q200) 1nF 16V X7R,16V X7R,ASSUMED,TDK CGA / Samsung CL-AEC (AEC-Q200),Fit,Reset glitch filter (ASSUMED)
"C59,C60",2,DNP,C_0402_1005Metric,Murata,GCM-series (AEC-Q200) DNP 50V C0G,50V C0G,FAMILY,TDK CGA / Samsung CL-AEC (AEC-Q200),DNP,Internal cap array used (SWRA834A 3.1.1); pads for tuning only
"C61,C62",2,15pF,C_0402_1005Metric,Murata,GCM-series (AEC-Q200) 15pF 50V C0G,50V C0G,FAMILY,TDK CGA / Samsung CL-AEC (AEC-Q200),Fit,LFXT load caps 15pF (TI ref CA2/C91)
C70,1,1.2pF,C_0402_1005Metric,Murata,GCM-series (AEC-Q200) 1.2pF 50V C0G,C0G +/-0.1pF,ASSUMED,TDK CGA / Samsung CL-AEC (AEC-Q200),Fit,"RF LPF shunt (TI LP-EM-CC2340R53 value list: 1.2pF) - topology/values UNVERIFIED, tune with VNA"
C71,1,0.7pF,C_0402_1005Metric,Murata,GCM-series (AEC-Q200) 0.7pF 50V C0G,C0G +/-0.05pF,ASSUMED,TDK CGA / Samsung CL-AEC (AEC-Q200),Fit,RF LPF shunt (TI ref 0.7pF)
"C73,C74",2,1.5pF,C_0402_1005Metric,Murata,GCM-series (AEC-Q200) 1.5pF 50V C0G,50V C0G,ASSUMED,TDK CGA / Samsung CL-AEC (AEC-Q200),DNP,Pi-match ANT1 shunt (DNP start) | Pi-match ANT3 shunt (DNP start)
D1,1,SMDJ36CA,D_SMC,Littelfuse,SMDJ36CA,"3000W bidirectional, VRWM 36V, Vc(max) 58.1V @51.6A, AEC-Q101 (Littelfuse)",VERIFIED,,Fit,"Local suppression sized for centrally-suppressed load dump (ISO16750-2 test B, Us*=58V). Unsuppressed 24V load dump (151-202V) needs an upstream central suppressor."
D2,1,Yellow (charging),LED_0603_1608Metric,Lite-On,LTST-C193KSKT-5A,"0603 yellow, AEC-Q101 variant to select",ASSUMED,,Fit,
D3,1,PESD2CAN,SOT-23,Nexperia,"PESD2CAN,215","VRWM 24V, Vcl 41V @5A, 30kV ESD, AEC-Q101",VERIFIED,,Fit,"Placed at J1, before the choke. Suits 12V and 24V (J1939) buses."
D4,1,Green (status),LED_0603_1608Metric,Lite-On,LTST-C193KGKT-5A,0603 green (AEC-Q101 variant to select),ASSUMED,,Fit,
F1,1,"1A fast, 125V",Fuse_Littelfuse-NANO2-451_453,Littelfuse,0451001.MRL,"1A, 125V, very-fast-acting NANO2 (source: Littelfuse)",VERIFIED,,Fit,Fuse must ride through inrush; I2t vs. TVS surge to be validated. Non-AEC-Q200 - replace with 0451001.MRL-AEC variant / Littelfuse 0453 if required.
FB1,1,0,L_0603_1608Metric,Murata,BLM18PG221SN1D,,FAMILY,,Fit,Ferrite bead 220R@100MHz / 2A (AEC-Q200) between V6P0 and TCAN VSUP; 0R jumper if bead not wanted.
"FID1,FID2,FID3",3,Fid,Fiducial_1mm_Mask2mm,n/a,Fiducial 1mm,n/a,VERIFIED,,Fit,
"H1,H2,H3,H4",4,M3 GND,MountingHole_3.2mm_M3_Pad_Via,n/a,M3 plated hole,"3.2mm, plated, GND",VERIFIED,,Fit,
J1,1,Micro-Fit 3.0 2x3 (43045-0612),Molex_Micro-Fit_3.0_43045-0612_2x03_P3.00mm_Vertical,Molex,43045-0612,"Micro-Fit 3.0 2x3 vertical THT, 5A/circuit, -40..105C",FAMILY,,Fit,"Mating harness assumed: pins 1/4 = VBAT/GND pair, 2/5 = CAN_H/CAN_L pair, 3 = IGN/WAKE, 6 = GND/drain. Automotive-grade alternative: Molex MX150 / TE MQS."
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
